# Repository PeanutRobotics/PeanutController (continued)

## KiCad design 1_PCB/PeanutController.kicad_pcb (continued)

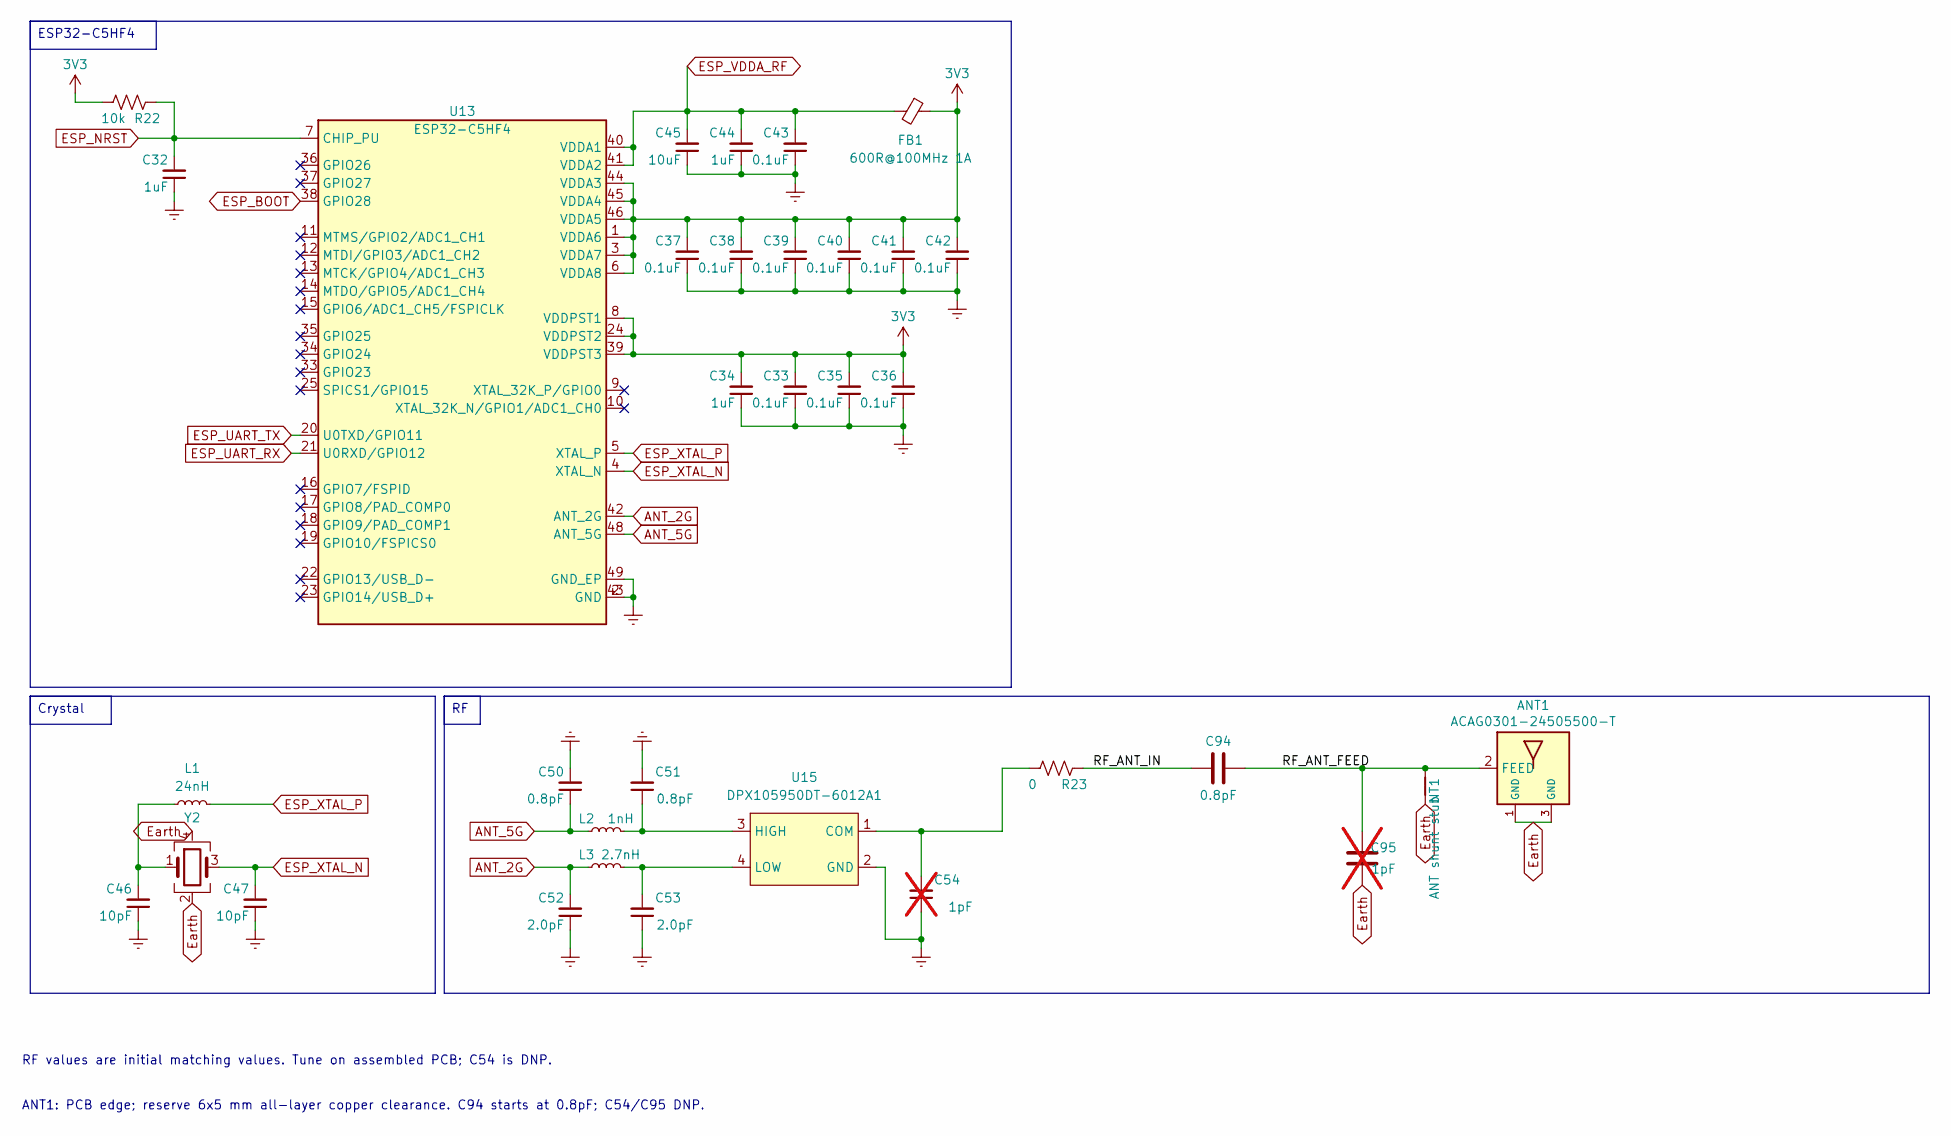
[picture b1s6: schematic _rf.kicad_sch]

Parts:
ANT1: ACAG0301-24505500-T; Abracon_ACAG0301_24505500_T
C32, C34, C44: 1uF; C_0402_1005Metric
C33, C35, C36, C37, C38, C39, C40, C41, C42, C43: 0.1uF; C_0402_1005Metric
C45: 10uF; C_0402_1005Metric
C46, C47: 10pF; C_0402_1005Metric
C50, C51: 0.8pF; C_0201_0603Metric
C52, C53: 2.0pF; C_0201_0603Metric
C54: 1pF; C_0201_0603Metric; not fitted
C94: 0.8pF; C_0402_1005Metric
C95: 1pF; C_0402_1005Metric; not fitted
FB1: 600R@100MHz 1A; L_0603_1608Metric
L1: 24nH; L_0402_1005Metric
L2: 1nH; L_0201_0603Metric
L3: 2.7nH; L_0201_0603Metric
NT1: ANT shunt stub; ANT_ShuntStub_0.5x2.5mm
R22: 10k; R_0402_1005Metric
R23: 0; R_0201_0603Metric
U13: ESP32-C5HF4; ESP32-C5_QFN48_6x6mm_P0.4mm_EP4.7x4.7mm
U15: DPX105950DT-6012A1; TDK_DPX105950DT_6012A1
Y2: 48MHz CL7pF 10ppm; Crystal_NDK_NX2016SA

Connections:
3V3: C33.2, C34.2, C35.2, C36.2, C37.2, C38.2, C39.2, C40.2, C41.2, C42.2, FB1.1, R22.2, U13.1 (VDDA6), U13.3 (VDDA7), U13.6 (VDDA8), U13.8 (VDDPST1), U13.24 (VDDPST2), U13.39 (VDDPST3), U13.44 (VDDA3), U13.45 (VDDA4), U13.46 (VDDA5); also elsewhere on the board
/RF/RF_ANT_FEED: ANT1.2 (FEED), C94.2, C95.1, NT1.1
/RF/RF_ANT_IN: C94.1, R23.1
ANT_2G: C52.2, L3.1, U13.42 (ANT_2G)
ANT_5G: C50.1, L2.1, U13.48 (ANT_5G)
ESP_BOOT: U13.38 (GPIO28); also elsewhere on the board
ESP_NRST: C32.2, R22.1, U13.7 (CHIP_PU); also elsewhere on the board
ESP_UART_RX: U13.21 (U0RXD/GPIO12); also elsewhere on the board
ESP_UART_TX: U13.20 (U0TXD/GPIO11); also elsewhere on the board
ESP_VDDA_RF: C43.2, C44.2, C45.2, FB1.2, U13.40 (VDDA1), U13.41 (VDDA2)
ESP_XTAL_N: C47.2, U13.4 (XTAL_N), Y2.3
ESP_XTAL_P: L1.2, U13.5 (XTAL_P)
Earth: ANT1.1 (GND), ANT1.3 (GND), C32.1, C33.1, C34.1, C35.1, C36.1, C37.1, C38.1, C39.1, C40.1, C41.1, C42.1, C43.1, C44.1, C45.1, C46.1, C47.1, C50.2, C51.2, C52.1, C53.1, C54.1, C95.2, NT1.2, U13.2 (GND), U13.43 (GND), U13.47 (GND), U13.49 (GND_EP), U15.2 (GND), Y2.2 (G), Y2.4 (CASE4); also elsewhere on the board
unnamed: C46.2, L1.1, Y2.1
unnamed: C54.2, R23.2, U15.1 (COM)
unnamed: C51.1, L2.2, U15.3 (HIGH)
unnamed: C53.2, L3.2, U15.4 (LOW)

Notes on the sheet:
ANT1: PCB edge; reserve 6x5 mm all-layer copper clearance. C94 starts at 0.8pF; C54/C95 DNP.
RF values are initial matching values. Tune on assembled PCB; C54 is DNP.
Crystal
ESP32-C5HF4

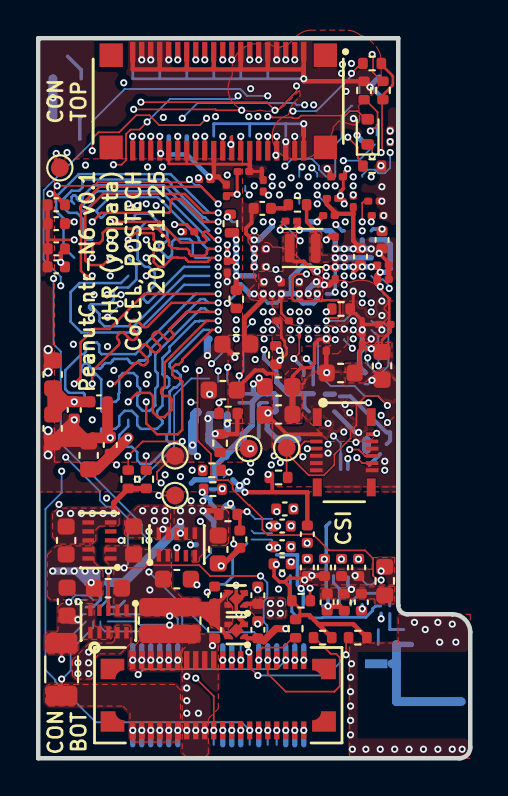
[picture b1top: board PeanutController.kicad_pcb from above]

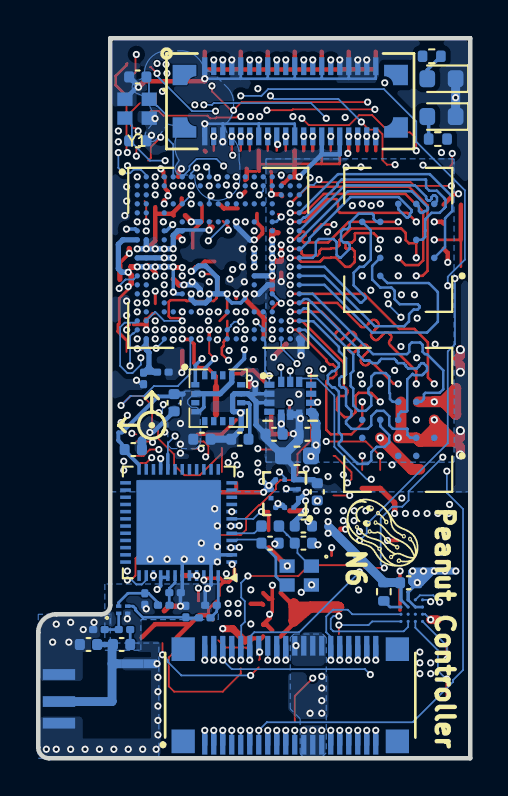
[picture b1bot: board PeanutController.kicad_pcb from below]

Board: 8 copper layers, 24.0 x 40.0 mm, 156 parts (47 on the bottom side), 131 nets.
